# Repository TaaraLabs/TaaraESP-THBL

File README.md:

TaaraESP THBL
=============

[WebSite](https://taaralabs.eu/eb1)

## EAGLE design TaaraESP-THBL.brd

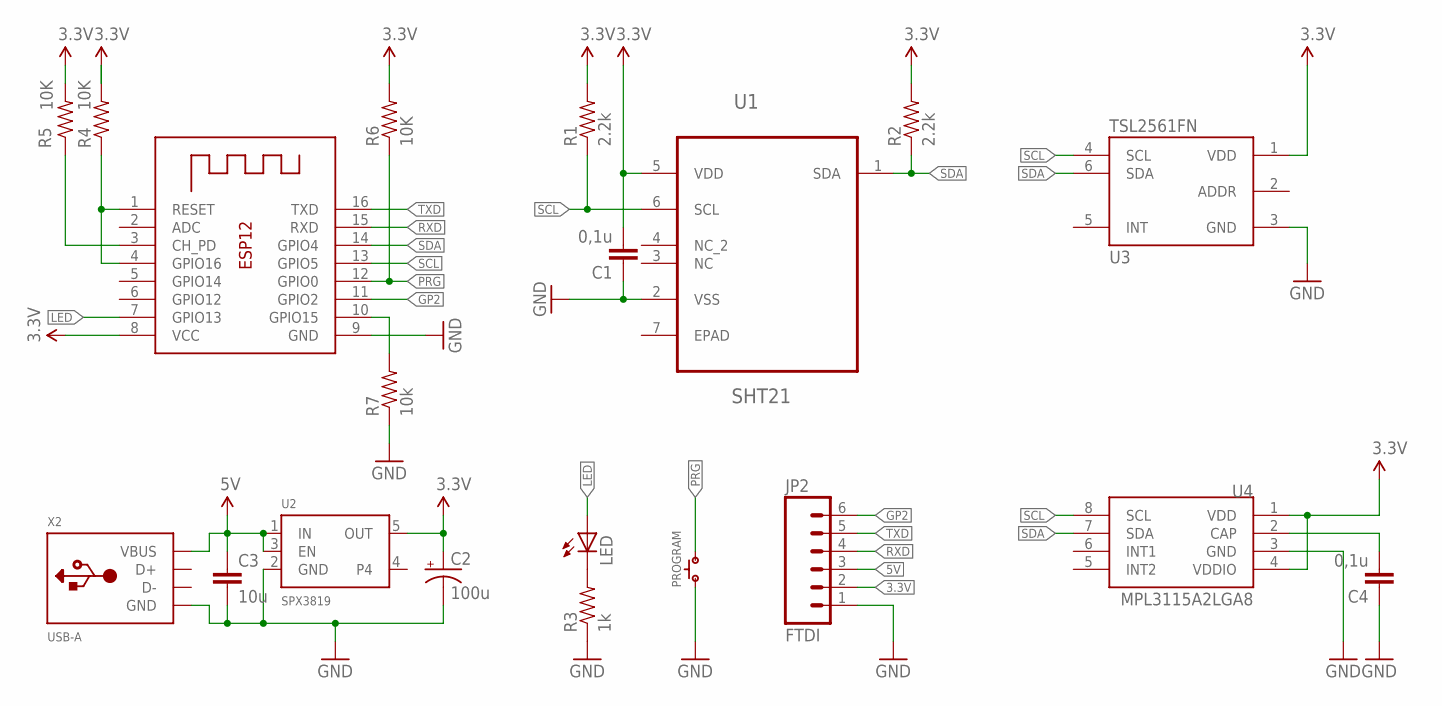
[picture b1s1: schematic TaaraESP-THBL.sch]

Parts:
C1, C4: 0,1u; 0603-CAP
C2: 100u; EIA3216
C3: 10u; 0603-CAP
JP2: FTDI; 1X06-SIP_LOCK
LED: LEDCHIPLED_0603; CHIPLED_0603
PROGRAM: SPST.B3U-1000P(M)-B; B3U-1000P(M)-B
R1, R2: 2.2k; 0603-RES
R3: 1k; 0603-RES
R4, R5, R6: 10K; 0603-RES
R7: 10k; 0603-RES
U1: SHT21; DFN300X300X110-7N
U2: SPX3819; SOT23-5
U3: TSL2561FN; FN-6
U4: MPL3115A2LGA8; LGA8
X1: ESP-12
X2: USB-A; MOLEX_480371000

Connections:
3.3V: C1.2, C2.A (+), JP2.2, R1.2, R2.2, R4.2, R5.2, R6.2, U1.5 (VDD), U2.5 (OUT), U3.1 (VDD), U4.1 (VDD), U4.4 (VDDIO), X1.8 (VCC)
5V: C3.1, JP2.3, U2.1 (IN), U2.3 (EN), X2.1 (VBUS)
GND: C1.1, C2.C (-), C3.2, C4.1, JP2.1, PROGRAM.1, R3.1, R7.1, U1.2 (VSS), U2.2 (GND), U3.3 (GND), U4.3 (GND), X1.9 (GND), X2.4 (GND)
GP2: JP2.6, X1.11 (GPIO2)
LED: LED.A, X1.7 (GPIO13)
unnamed: LED.C, R3.2
unnamed: R4.1, X1.1 (RESET), X1.4 (GPIO16)
unnamed: R5.1, X1.3 (CH_PD)
unnamed: R7.2, X1.10 (GPIO15)
unnamed: C4.2, U4.2 (CAP)
PRG: PROGRAM.2, R6.1, X1.12 (GPIO0)
RXD: JP2.4, X1.15 (RXD)
SCL: R1.1, U1.6 (SCL), U3.4 (SCL), U4.8 (SCL), X1.13 (GPIO5)
SDA: R2.1, U1.1 (SDA), U3.6 (SDA), U4.7 (SDA), X1.14 (GPIO4)
TXD: JP2.5, X1.16 (TXD)

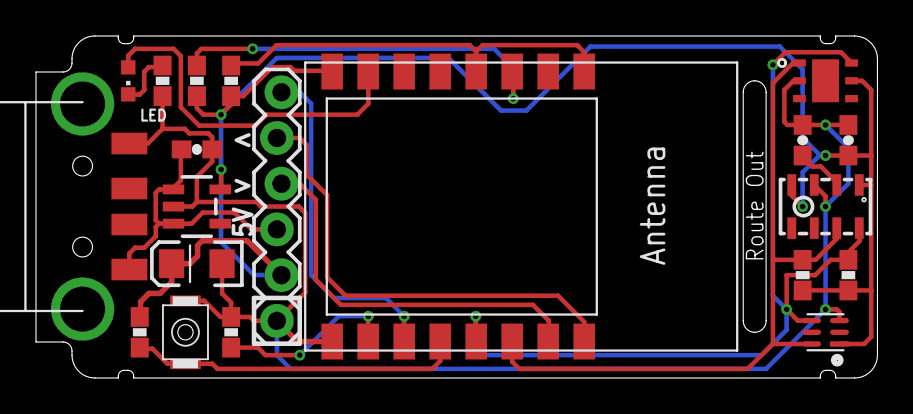
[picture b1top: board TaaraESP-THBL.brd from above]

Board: 2 copper layers, 46.7 x 19.0 mm, 21 parts (1 on the bottom side), 15 nets.

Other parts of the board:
U$5: OSHW-LOGO-S

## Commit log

2016-11-20 Gereber files moved to zip file
2016-11-20 Removed Eagle lock files
2016-11-20 moved GTP to the gerbers ZIP archive
2016-11-20 Added README.md file

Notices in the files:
parts and their libraries:
microbuilder: This work is placed in the public domain, and may be freely used for commercial and non-commercial work with the following conditions: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
SparkFun-Aesthetics: Licensing: CC v3.0 Share-Alike You are welcome to use this library for commercial purposes.
